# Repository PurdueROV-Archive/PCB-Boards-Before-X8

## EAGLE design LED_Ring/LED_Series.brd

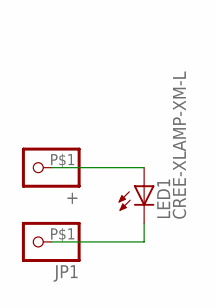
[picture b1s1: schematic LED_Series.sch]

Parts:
+: PINHD-1X1; 1X01
JP1: PINHD-1X1; 1X01
LED1: CREE-XLAMP-XM-L

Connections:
AN: JP1.P$1, LED1.C, LED1.C@1 (C)
CAT: +.P$1, LED1.A, LED1.A@1 (A)

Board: 2 copper layers, 3 parts (0 on the bottom side), 2 nets, no tracks yet.

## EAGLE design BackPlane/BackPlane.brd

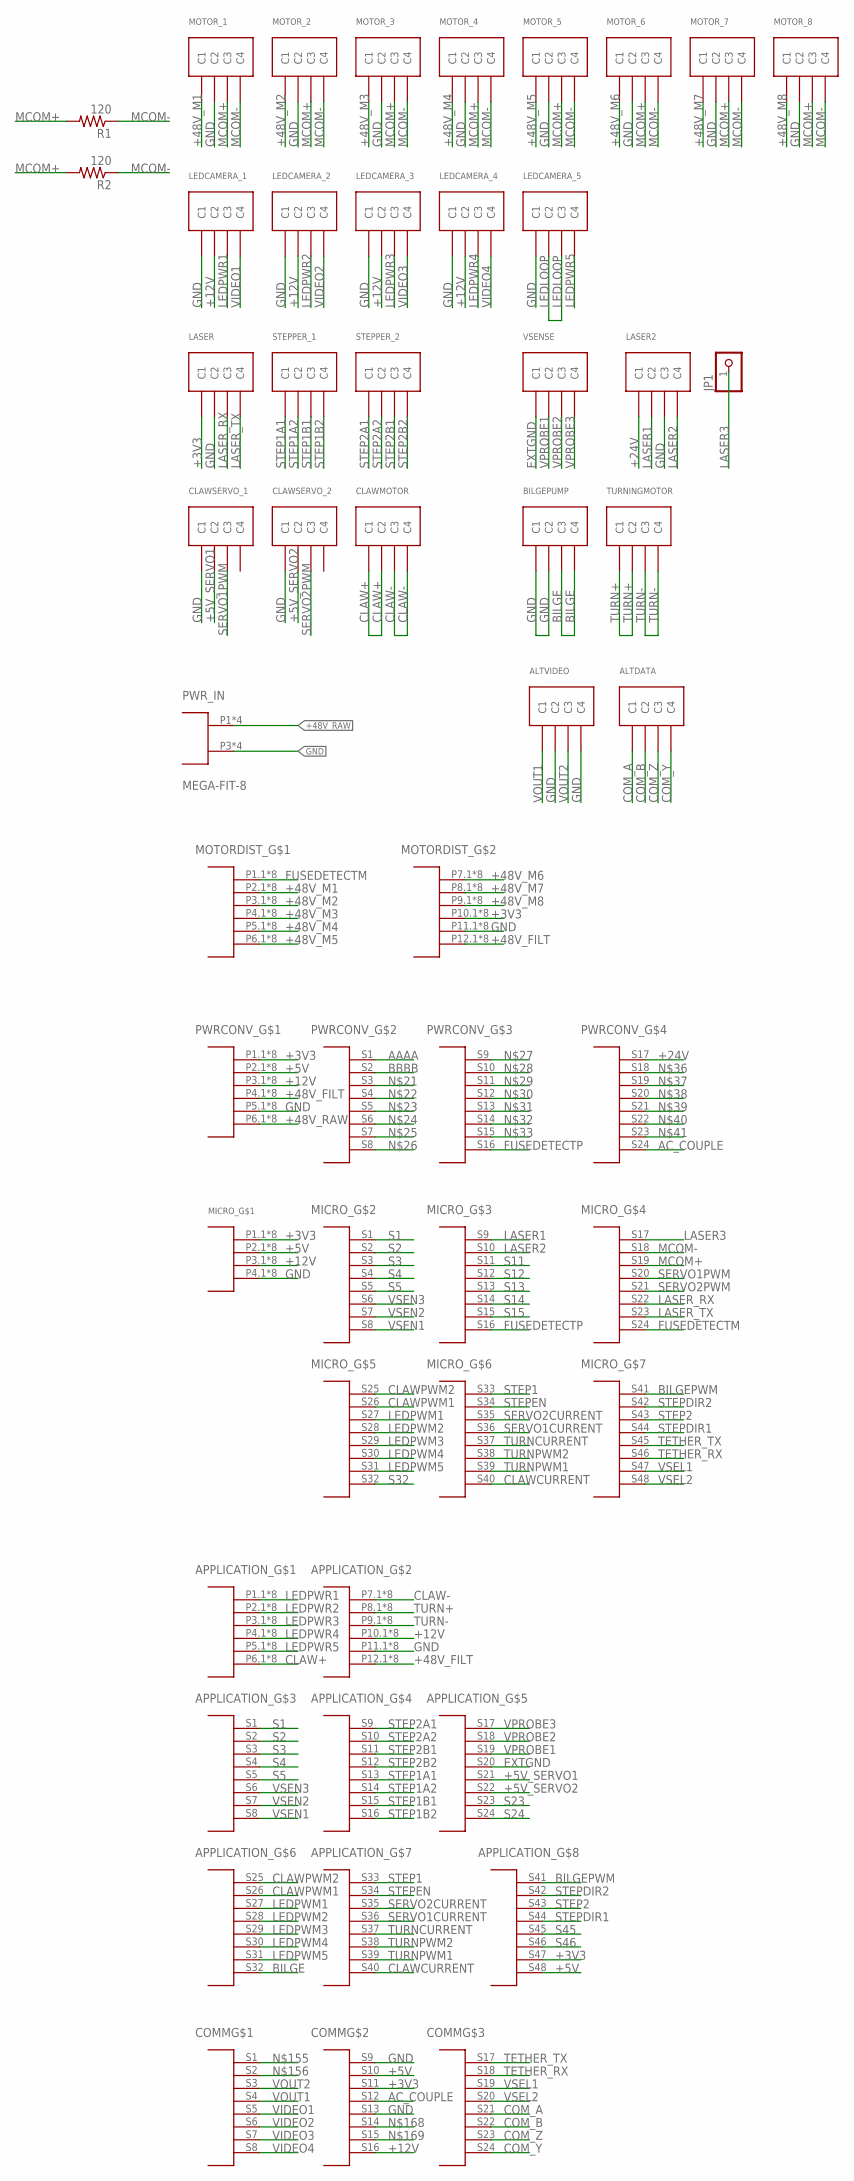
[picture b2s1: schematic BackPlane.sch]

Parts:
ALTDATA: MICRO-FIT-4-SMD-PART; MIRCO-FIT-4-SMD
ALTVIDEO: MICRO-FIT-4-SMD-PART; MIRCO-FIT-4-SMD
APPLICATION_: TEN60-P6-S24-S24-P6-VERT
BILGEPUMP: MICRO-FIT-4-SMD-PART; MIRCO-FIT-4-SMD
CLAWMOTOR: MICRO-FIT-4-SMD-PART; MIRCO-FIT-4-SMD
CLAWSERVO_1, CLAWSERVO_2: MICRO-FIT-4-SMD-PART; MIRCO-FIT-4-SMD
COMM: TEN60-S24-RA
JP1: PINHD-1X1; 1X01
LASER, LASER2: MICRO-FIT-4-SMD-PART; MIRCO-FIT-4-SMD
LEDCAMERA_1, LEDCAMERA_2, LEDCAMERA_3, LEDCAMERA_4, LEDCAMERA_5: MICRO-FIT-4-SMD-PART; MIRCO-FIT-4-SMD
MICRO_: TEN60-S24-S24-P4-VERT
MOTORDIST_: TEN60-P6-P6-VERT
MOTOR_1, MOTOR_2, MOTOR_3, MOTOR_4, MOTOR_5, MOTOR_6, MOTOR_7, MOTOR_8: MICRO-FIT-4-SMD-PART; MIRCO-FIT-4-SMD
PWRCONV_: TEN60-S24-P6-VERT
PWR_IN: MEGA-FIT-8
R1, R2: 120; R0603
STEPPER_1, STEPPER_2: MICRO-FIT-4-SMD-PART; MIRCO-FIT-4-SMD
TURNINGMOTOR: MICRO-FIT-4-SMD-PART; MIRCO-FIT-4-SMD
VSENSE: MICRO-FIT-4-SMD-PART; MIRCO-FIT-4-SMD

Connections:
+3V3: APPLICATION_.S47, COMM.S11, LASER.C1, MICRO_.P1.1, MICRO_.P1.2, MICRO_.P1.3, MICRO_.P1.4, MICRO_.P1.5, MICRO_.P1.6, MICRO_.P1.7, MICRO_.P1.8, MOTORDIST_.P10.1, MOTORDIST_.P10.2, MOTORDIST_.P10.3, MOTORDIST_.P10.4, MOTORDIST_.P10.5, MOTORDIST_.P10.6, MOTORDIST_.P10.7, MOTORDIST_.P10.8, PWRCONV_.P1.1, PWRCONV_.P1.2, PWRCONV_.P1.3, PWRCONV_.P1.4, PWRCONV_.P1.5, PWRCONV_.P1.6, PWRCONV_.P1.7, PWRCONV_.P1.8
+5V: APPLICATION_.S48, COMM.S10, MICRO_.P2.1, MICRO_.P2.2, MICRO_.P2.3, MICRO_.P2.4, MICRO_.P2.5, MICRO_.P2.6, MICRO_.P2.7, MICRO_.P2.8, PWRCONV_.P2.1, PWRCONV_.P2.2, PWRCONV_.P2.3, PWRCONV_.P2.4, PWRCONV_.P2.5, PWRCONV_.P2.6, PWRCONV_.P2.7, PWRCONV_.P2.8
+5V_SERVO1: APPLICATION_.S21, CLAWSERVO_1.C2
+5V_SERVO2: APPLICATION_.S22, CLAWSERVO_2.C2
+12V: APPLICATION_.P10.1, APPLICATION_.P10.2, APPLICATION_.P10.3, APPLICATION_.P10.4, APPLICATION_.P10.5, APPLICATION_.P10.6, APPLICATION_.P10.7, APPLICATION_.P10.8, COMM.S16, LEDCAMERA_1.C2, LEDCAMERA_2.C2, LEDCAMERA_3.C2, LEDCAMERA_4.C2, MICRO_.P3.1, MICRO_.P3.2, MICRO_.P3.3, MICRO_.P3.4, MICRO_.P3.5, MICRO_.P3.6, MICRO_.P3.7, MICRO_.P3.8, PWRCONV_.P3.1, PWRCONV_.P3.2, PWRCONV_.P3.3, PWRCONV_.P3.4, PWRCONV_.P3.5, PWRCONV_.P3.6, PWRCONV_.P3.7, PWRCONV_.P3.8
+24V: LASER2.C1, PWRCONV_.S17
+48V_FILT: APPLICATION_.P12.1, APPLICATION_.P12.2, APPLICATION_.P12.3, APPLICATION_.P12.4, APPLICATION_.P12.5, APPLICATION_.P12.6, APPLICATION_.P12.7, APPLICATION_.P12.8, MOTORDIST_.P12.1, MOTORDIST_.P12.2, MOTORDIST_.P12.3, MOTORDIST_.P12.4, MOTORDIST_.P12.5, MOTORDIST_.P12.6, MOTORDIST_.P12.7, MOTORDIST_.P12.8, PWRCONV_.P4.1, PWRCONV_.P4.2, PWRCONV_.P4.3, PWRCONV_.P4.4, PWRCONV_.P4.5, PWRCONV_.P4.6, PWRCONV_.P4.7, PWRCONV_.P4.8
+48V_M1: MOTORDIST_.P2.1, MOTORDIST_.P2.2, MOTORDIST_.P2.3, MOTORDIST_.P2.4, MOTORDIST_.P2.5, MOTORDIST_.P2.6, MOTORDIST_.P2.7, MOTORDIST_.P2.8, MOTOR_1.C1
+48V_M2: MOTORDIST_.P3.1, MOTORDIST_.P3.2, MOTORDIST_.P3.3, MOTORDIST_.P3.4, MOTORDIST_.P3.5, MOTORDIST_.P3.6, MOTORDIST_.P3.7, MOTORDIST_.P3.8, MOTOR_2.C1
+48V_M3: MOTORDIST_.P4.1, MOTORDIST_.P4.2, MOTORDIST_.P4.3, MOTORDIST_.P4.4, MOTORDIST_.P4.5, MOTORDIST_.P4.6, MOTORDIST_.P4.7, MOTORDIST_.P4.8, MOTOR_3.C1
+48V_M4: MOTORDIST_.P5.1, MOTORDIST_.P5.2, MOTORDIST_.P5.3, MOTORDIST_.P5.4, MOTORDIST_.P5.5, MOTORDIST_.P5.6, MOTORDIST_.P5.7, MOTORDIST_.P5.8, MOTOR_4.C1
+48V_M5: MOTORDIST_.P6.1, MOTORDIST_.P6.2, MOTORDIST_.P6.3, MOTORDIST_.P6.4, MOTORDIST_.P6.5, MOTORDIST_.P6.6, MOTORDIST_.P6.7, MOTORDIST_.P6.8, MOTOR_5.C1
+48V_M6: MOTORDIST_.P7.1, MOTORDIST_.P7.2, MOTORDIST_.P7.3, MOTORDIST_.P7.4, MOTORDIST_.P7.5, MOTORDIST_.P7.6, MOTORDIST_.P7.7, MOTORDIST_.P7.8, MOTOR_6.C1
+48V_M7: MOTORDIST_.P8.1, MOTORDIST_.P8.2, MOTORDIST_.P8.3, MOTORDIST_.P8.4, MOTORDIST_.P8.5, MOTORDIST_.P8.6, MOTORDIST_.P8.7, MOTORDIST_.P8.8, MOTOR_7.C1
+48V_M8: MOTORDIST_.P9.1, MOTORDIST_.P9.2, MOTORDIST_.P9.3, MOTORDIST_.P9.4, MOTORDIST_.P9.5, MOTORDIST_.P9.6, MOTORDIST_.P9.7, MOTORDIST_.P9.8, MOTOR_8.C1
+48V_RAW: PWRCONV_.P6.1, PWRCONV_.P6.2, PWRCONV_.P6.3, PWRCONV_.P6.4, PWRCONV_.P6.5, PWRCONV_.P6.6, PWRCONV_.P6.7, PWRCONV_.P6.8, PWR_IN.P1, PWR_IN.P2, PWR_IN.P5, PWR_IN.P6
AAAA: PWRCONV_.S1
AC_COUPLE: COMM.S12, PWRCONV_.S24
BBBB: PWRCONV_.S2
BILGE: APPLICATION_.S32, BILGEPUMP.C3, BILGEPUMP.C4
BILGEPWM: APPLICATION_.S41, MICRO_.S41
CLAW+: APPLICATION_.P6.1, APPLICATION_.P6.2, APPLICATION_.P6.3, APPLICATION_.P6.4, APPLICATION_.P6.5, APPLICATION_.P6.6, APPLICATION_.P6.7, APPLICATION_.P6.8, CLAWMOTOR.C1, CLAWMOTOR.C2
CLAW-: APPLICATION_.P7.1, APPLICATION_.P7.2, APPLICATION_.P7.3, APPLICATION_.P7.4, APPLICATION_.P7.5, APPLICATION_.P7.6, APPLICATION_.P7.7, APPLICATION_.P7.8, CLAWMOTOR.C3, CLAWMOTOR.C4
CLAWCURRENT: APPLICATION_.S40, MICRO_.S40
CLAWPWM1: APPLICATION_.S26, MICRO_.S26
CLAWPWM2: APPLICATION_.S25, MICRO_.S25
COM_A: ALTDATA.C1, COMM.S21
COM_B: ALTDATA.C2, COMM.S22
COM_Y: ALTDATA.C4, COMM.S24
COM_Z: ALTDATA.C3, COMM.S23
EXTGND: APPLICATION_.S20, VSENSE.C1
FUSEDETECTM: MICRO_.S24, MOTORDIST_.P1.1, MOTORDIST_.P1.2, MOTORDIST_.P1.3, MOTORDIST_.P1.4, MOTORDIST_.P1.5, MOTORDIST_.P1.6, MOTORDIST_.P1.7, MOTORDIST_.P1.8
FUSEDETECTP: MICRO_.S16, PWRCONV_.S16
GND: ALTVIDEO.C2, ALTVIDEO.C4, APPLICATION_.P11.1, APPLICATION_.P11.2, APPLICATION_.P11.3, APPLICATION_.P11.4, APPLICATION_.P11.5, APPLICATION_.P11.6, APPLICATION_.P11.7, APPLICATION_.P11.8, BILGEPUMP.C1, BILGEPUMP.C2, CLAWSERVO_1.C1, CLAWSERVO_2.C1, COMM.S9, COMM.S13, LASER.C2, LASER2.C3, LEDCAMERA_1.C1, LEDCAMERA_2.C1, LEDCAMERA_3.C1, LEDCAMERA_4.C1, LEDCAMERA_5.C1, MICRO_.P4.1, MICRO_.P4.2, MICRO_.P4.3, MICRO_.P4.4, MICRO_.P4.5, MICRO_.P4.6, MICRO_.P4.7, MICRO_.P4.8, MOTORDIST_.P11.1, MOTORDIST_.P11.2, MOTORDIST_.P11.3, MOTORDIST_.P11.4, MOTORDIST_.P11.5, MOTORDIST_.P11.6, MOTORDIST_.P11.7, MOTORDIST_.P11.8, MOTOR_1.C2, MOTOR_2.C2, MOTOR_3.C2, MOTOR_4.C2, MOTOR_5.C2, MOTOR_6.C2, MOTOR_7.C2, MOTOR_8.C2, PWRCONV_.P5.1, PWRCONV_.P5.2, PWRCONV_.P5.3, PWRCONV_.P5.4, PWRCONV_.P5.5, PWRCONV_.P5.6, PWRCONV_.P5.7, PWRCONV_.P5.8, PWR_IN.P3, PWR_IN.P4, PWR_IN.P7, PWR_IN.P8
LASER1: LASER2.C2, MICRO_.S9
LASER2: LASER2.C4, MICRO_.S10
LASER3: JP1.1, MICRO_.S17
LASER_RX: LASER.C3, MICRO_.S22
LASER_TX: LASER.C4, MICRO_.S23
LEDLOOP: LEDCAMERA_5.C2, LEDCAMERA_5.C3
LEDPWM1: APPLICATION_.S27, MICRO_.S27
LEDPWM2: APPLICATION_.S28, MICRO_.S28
LEDPWM3: APPLICATION_.S29, MICRO_.S29
LEDPWM4: APPLICATION_.S30, MICRO_.S30
LEDPWM5: APPLICATION_.S31, MICRO_.S31
LEDPWR1: APPLICATION_.P1.1, APPLICATION_.P1.2, APPLICATION_.P1.3, APPLICATION_.P1.4, APPLICATION_.P1.5, APPLICATION_.P1.6, APPLICATION_.P1.7, APPLICATION_.P1.8, LEDCAMERA_1.C3
LEDPWR2: APPLICATION_.P2.1, APPLICATION_.P2.2, APPLICATION_.P2.3, APPLICATION_.P2.4, APPLICATION_.P2.5, APPLICATION_.P2.6, APPLICATION_.P2.7, APPLICATION_.P2.8, LEDCAMERA_2.C3
LEDPWR3: APPLICATION_.P3.1, APPLICATION_.P3.2, APPLICATION_.P3.3, APPLICATION_.P3.4, APPLICATION_.P3.5, APPLICATION_.P3.6, APPLICATION_.P3.7, APPLICATION_.P3.8, LEDCAMERA_3.C3
LEDPWR4: APPLICATION_.P4.1, APPLICATION_.P4.2, APPLICATION_.P4.3, APPLICATION_.P4.4, APPLICATION_.P4.5, APPLICATION_.P4.6, APPLICATION_.P4.7, APPLICATION_.P4.8, LEDCAMERA_4.C3
LEDPWR5: APPLICATION_.P5.1, APPLICATION_.P5.2, APPLICATION_.P5.3, APPLICATION_.P5.4, APPLICATION_.P5.5, APPLICATION_.P5.6, APPLICATION_.P5.7, APPLICATION_.P5.8, LEDCAMERA_5.C4
MCOM+: MICRO_.S19, MOTOR_1.C3, MOTOR_2.C3, MOTOR_3.C3, MOTOR_4.C3, MOTOR_5.C3, MOTOR_6.C3, MOTOR_7.C3, MOTOR_8.C3, R1.2, R2.2
MCOM-: MICRO_.S18, MOTOR_1.C4, MOTOR_2.C4, MOTOR_3.C4, MOTOR_4.C4, MOTOR_5.C4, MOTOR_6.C4, MOTOR_7.C4, MOTOR_8.C4, R1.1, R2.1
S1: APPLICATION_.S1, MICRO_.S1
S2: APPLICATION_.S2, MICRO_.S2
S3: APPLICATION_.S3, MICRO_.S3
S4: APPLICATION_.S4, MICRO_.S4
S5: APPLICATION_.S5, MICRO_.S5
S11: MICRO_.S11
S12: MICRO_.S12
S13: MICRO_.S13
S14: MICRO_.S14
S15: MICRO_.S15
S23: APPLICATION_.S23
S24: APPLICATION_.S24
S32: MICRO_.S32
S45: APPLICATION_.S45
S46: APPLICATION_.S46
SERVO1CURRENT: APPLICATION_.S36, MICRO_.S36
SERVO1PWM: CLAWSERVO_1.C3, MICRO_.S20
SERVO2CURRENT: APPLICATION_.S35, MICRO_.S35
SERVO2PWM: CLAWSERVO_2.C3, MICRO_.S21
STEP1: APPLICATION_.S33, MICRO_.S33
STEP1A1: APPLICATION_.S13, STEPPER_1.C1
STEP1A2: APPLICATION_.S14, STEPPER_1.C2
STEP1B1: APPLICATION_.S15, STEPPER_1.C3
STEP1B2: APPLICATION_.S16, STEPPER_1.C4
STEP2: APPLICATION_.S43, MICRO_.S43
STEP2A1: APPLICATION_.S9, STEPPER_2.C1
STEP2A2: APPLICATION_.S10, STEPPER_2.C2
STEP2B1: APPLICATION_.S11, STEPPER_2.C3
STEP2B2: APPLICATION_.S12, STEPPER_2.C4
STEPDIR1: APPLICATION_.S44, MICRO_.S44
STEPDIR2: APPLICATION_.S42, MICRO_.S42
STEPEN: APPLICATION_.S34, MICRO_.S34
TETHER_RX: COMM.S18, MICRO_.S46
TETHER_TX: COMM.S17, MICRO_.S45
TURN+: APPLICATION_.P8.1, APPLICATION_.P8.2, APPLICATION_.P8.3, APPLICATION_.P8.4, APPLICATION_.P8.5, APPLICATION_.P8.6, APPLICATION_.P8.7, APPLICATION_.P8.8, TURNINGMOTOR.C1, TURNINGMOTOR.C2
TURN-: APPLICATION_.P9.1, APPLICATION_.P9.2, APPLICATION_.P9.3, APPLICATION_.P9.4, APPLICATION_.P9.5, APPLICATION_.P9.6, APPLICATION_.P9.7, APPLICATION_.P9.8, TURNINGMOTOR.C3, TURNINGMOTOR.C4
TURNCURRENT: APPLICATION_.S37, MICRO_.S37
TURNPWM1: APPLICATION_.S39, MICRO_.S39
TURNPWM2: APPLICATION_.S38, MICRO_.S38
VIDEO1: COMM.S5, LEDCAMERA_1.C4
VIDEO2: COMM.S6, LEDCAMERA_2.C4
VIDEO3: COMM.S7, LEDCAMERA_3.C4
VIDEO4: COMM.S8, LEDCAMERA_4.C4
VOUT1: ALTVIDEO.C1, COMM.S4
VOUT2: ALTVIDEO.C3, COMM.S3
VPROBE1: APPLICATION_.S19, VSENSE.C2
VPROBE2: APPLICATION_.S18, VSENSE.C3
VPROBE3: APPLICATION_.S17, VSENSE.C4
VSEL1: COMM.S19, MICRO_.S47
VSEL2: COMM.S20, MICRO_.S48
VSEN1: APPLICATION_.S8, MICRO_.S8
VSEN2: APPLICATION_.S7, MICRO_.S7
VSEN3: APPLICATION_.S6, MICRO_.S6

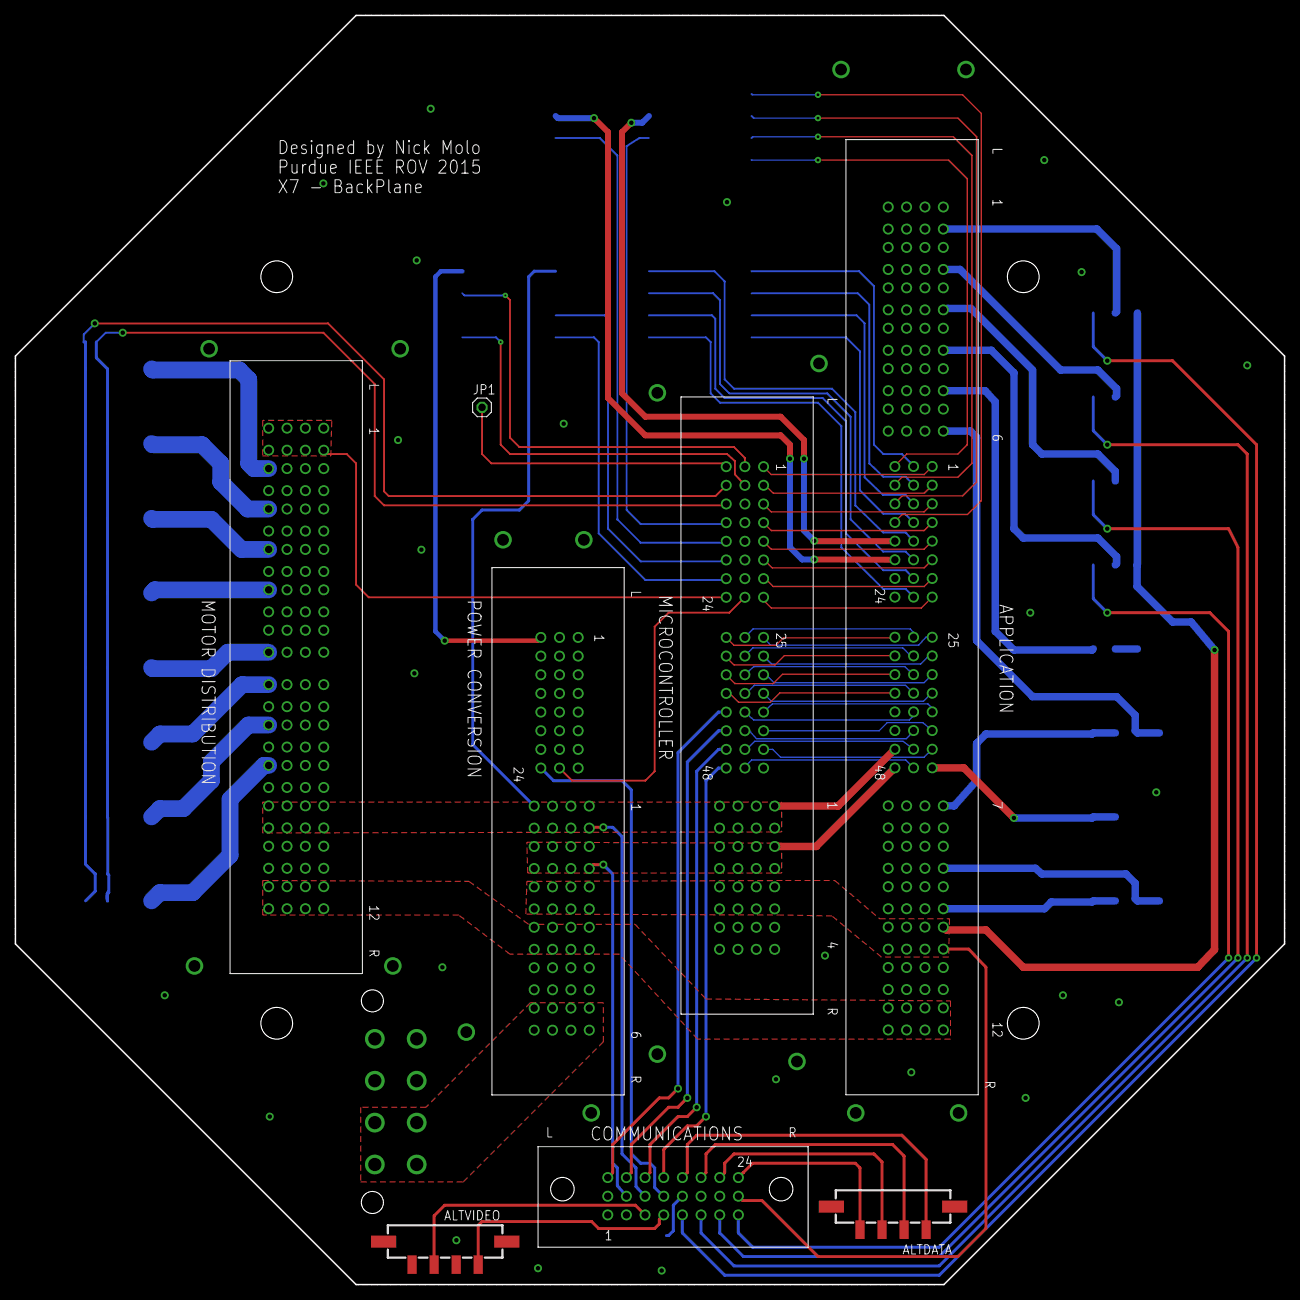
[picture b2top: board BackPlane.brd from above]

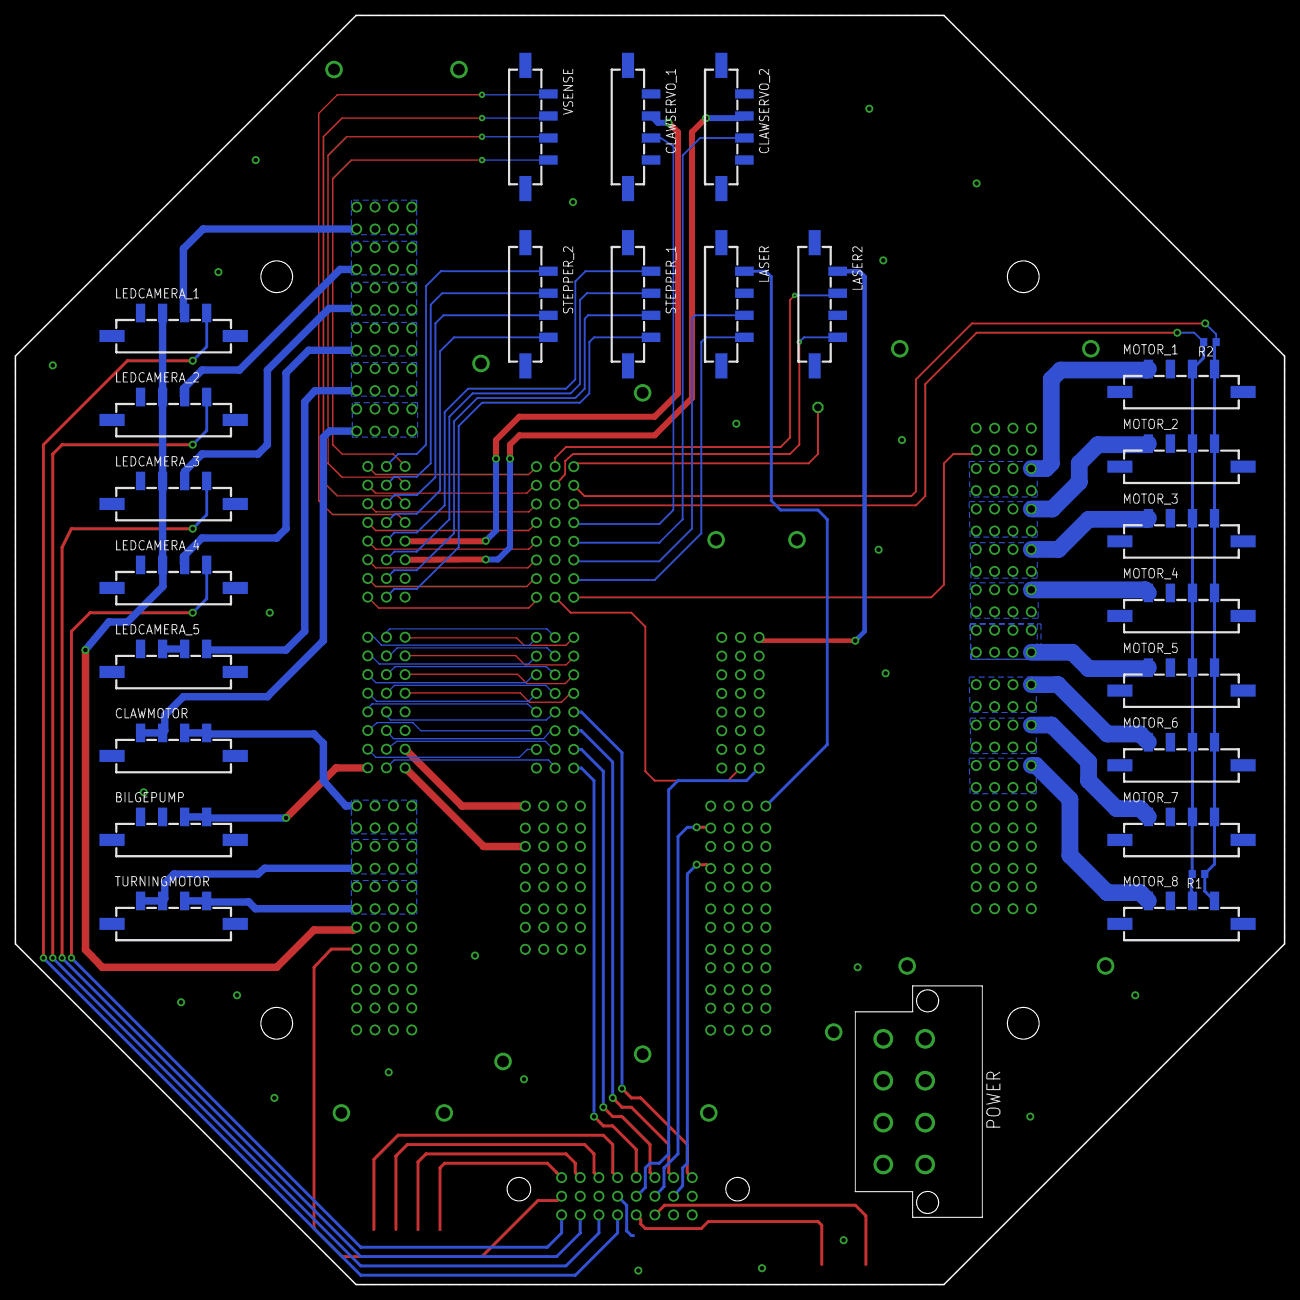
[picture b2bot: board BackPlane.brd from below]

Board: 2 copper layers, 172.7 x 172.7 mm, 34 parts (26 on the bottom side), 93 nets.

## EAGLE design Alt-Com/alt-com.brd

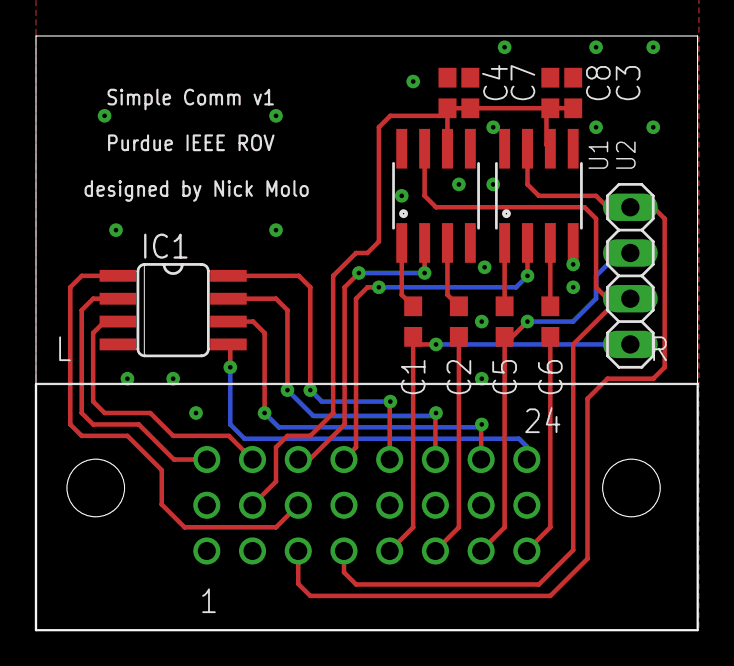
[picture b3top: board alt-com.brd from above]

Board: 2 copper layers, 36.8 x 33.0 mm, 13 parts (0 on the bottom side), 21 nets.

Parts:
C1, C2, C5, C6: 0.01uF; C0603
C3, C7: 0.1uF; C0603
C4, C8: 47uF; C0603
EMEREGENCY: 1X04
IC1: MAX3467CPA; SO08
U1, U2: SO08
U$1: TEN60-S24-RA

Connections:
+3V3: IC1.1, U$1.S11
+5V: C3.1, C4.1, C7.1, C8.1, U1.6, U2.6, U$1.S10
COM_A: IC1.8, U$1.S21
COM_B: IC1.7, U$1.S22
COM_Y: IC1.5, U$1.S24
COM_Z: IC1.6, U$1.S23
GND: C3.2, C4.2, C7.2, C8.2, IC1.4, U1.4, U1.8, U2.4, U2.8, U$1.S9
unnamed: C5.1, U2.1
unnamed: C6.1, U2.3
unnamed: C1.1, U1.1
unnamed: C2.1, U1.3
TETHER_RX: IC1.2, U$1.S17
TETHER_TX: IC1.3, U$1.S18
VIDEO1: C1.2, EMEREGENCY.1, U$1.S5
VIDEO2: C2.2, U$1.S6
VIDEO3: C5.2, EMEREGENCY.3, U$1.S7
VIDEO4: C6.2, U$1.S8
VOUT1: EMEREGENCY.2, U1.7, U$1.S4
VOUT2: EMEREGENCY.4, U2.7, U$1.S3
VSEL1: U1.2, U$1.S19
VSEL2: U2.2, U$1.S20

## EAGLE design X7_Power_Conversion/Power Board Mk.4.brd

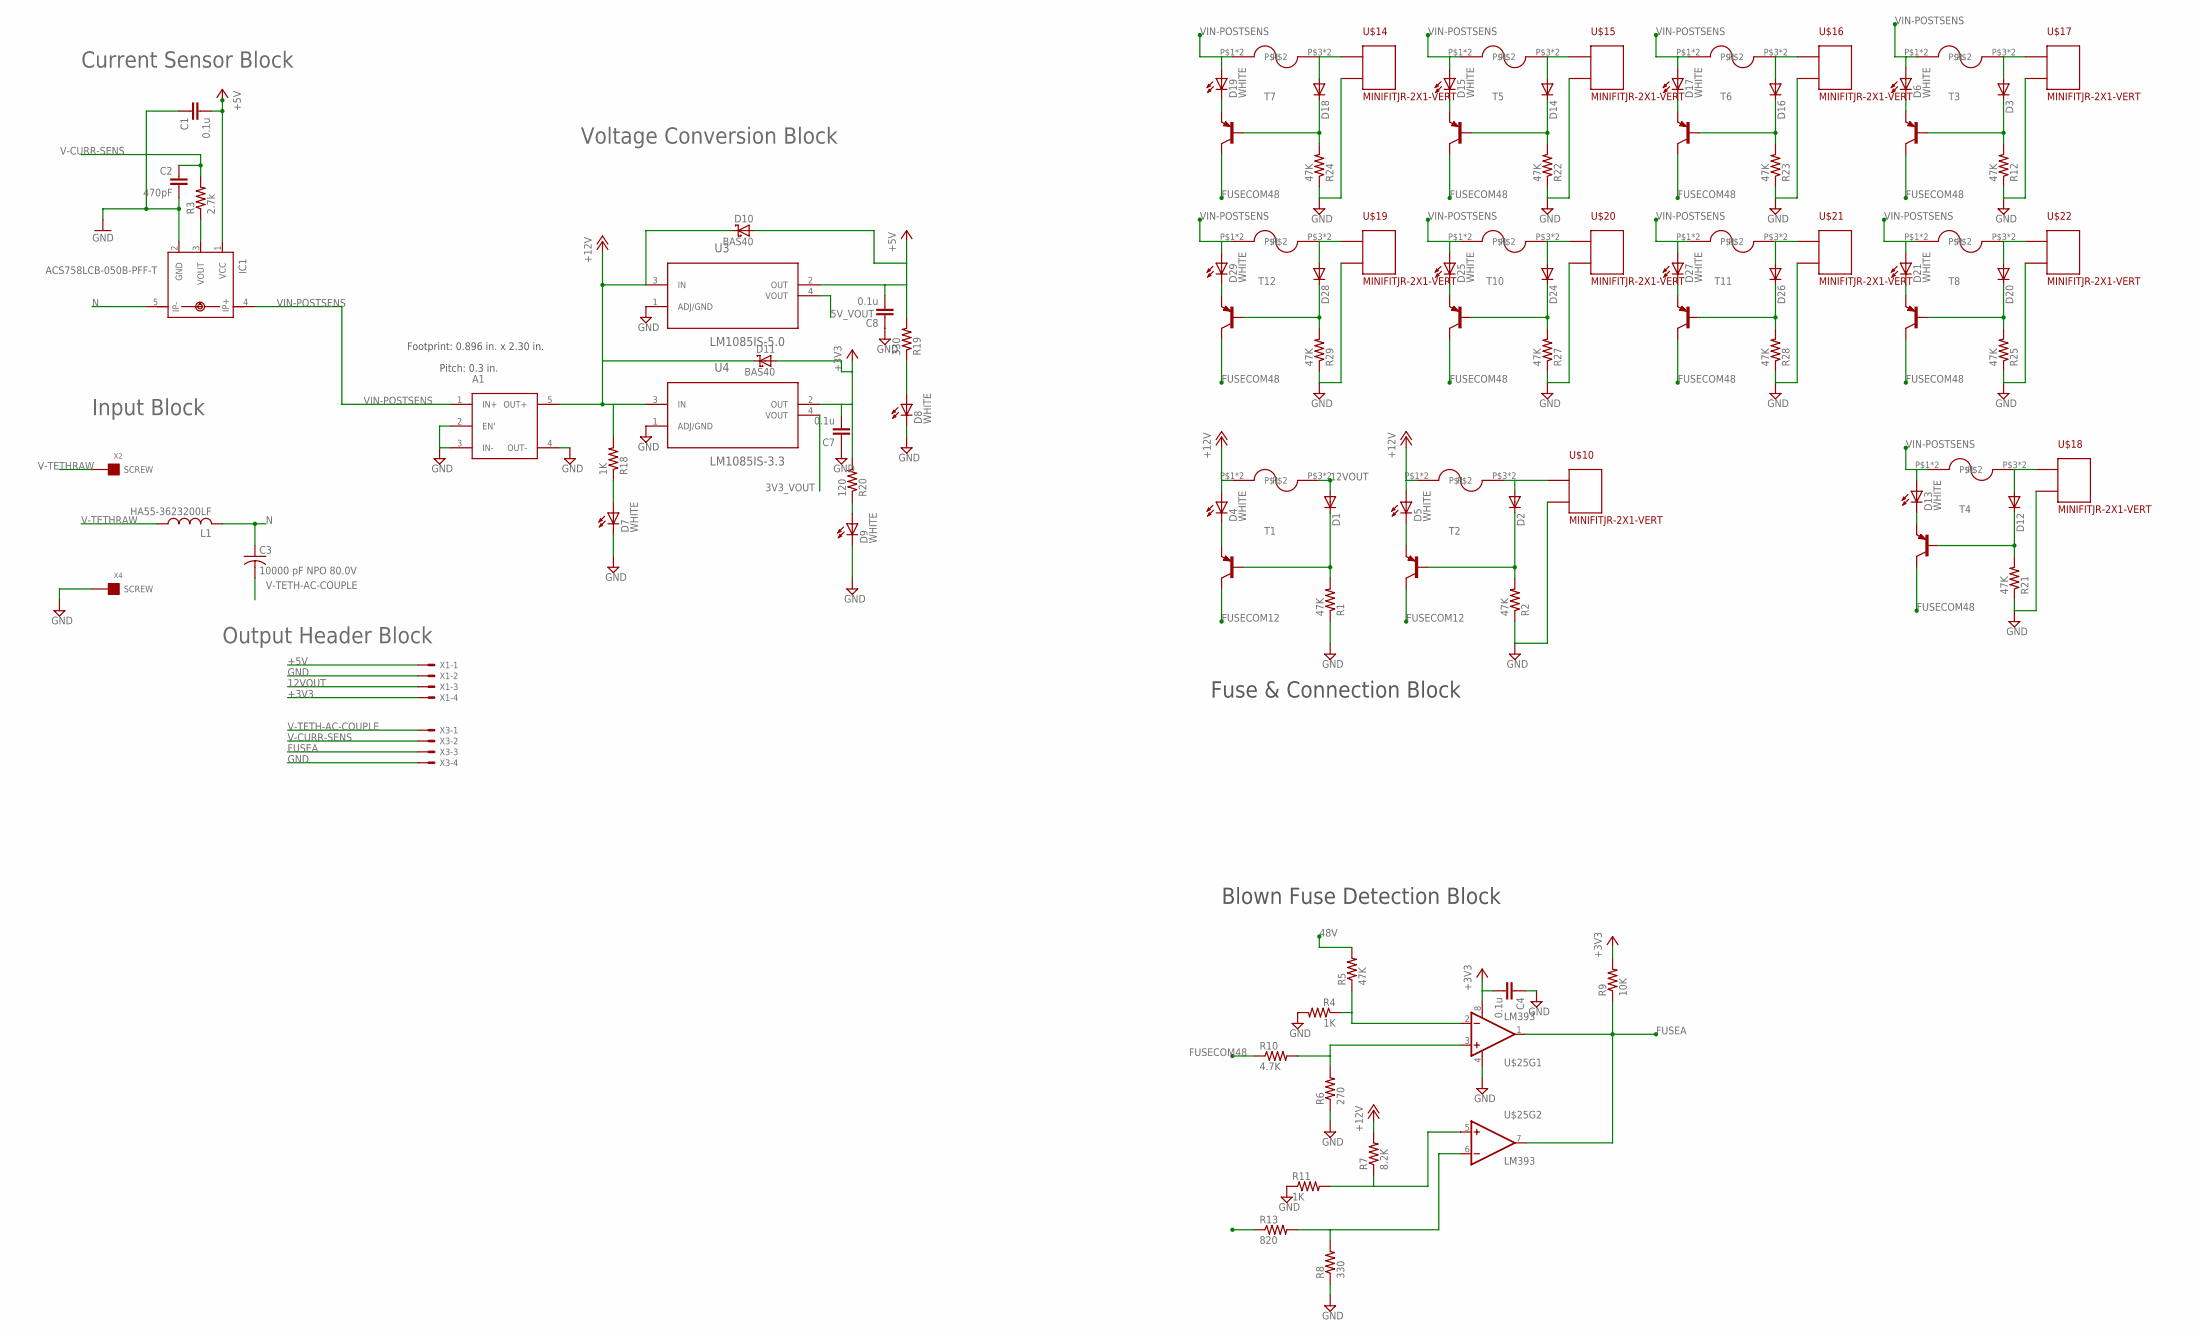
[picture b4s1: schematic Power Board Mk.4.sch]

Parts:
A1: SQE48T20120; BRICK
C1, C4, C7, C8: 0.1u; 0805
C2: 470pF; 0805
C3: 10000 pF NPO 80.0V; C0603
D1, D2, D3, D12, D14, D16, D18, D20, D24, D26, D28: DIODEHV; DIODE-HV
D4, D5, D6, D7, D8, D9, D13, D15, D17, D19, D21, D25, D27, D29: WHITE; LED-1206
D10, D11: BAS40; SOT23
IC1: ACS758LCB-050B-PFF-T; CB-PFF
L1: HA55-3623200LF; THIND
R1, R2, R5, R12, R21, R22, R23, R24, R25, R27, R28, R29: 47K; 0805
R3: 2.7k; 0805
R4, R11, R18: 1K; 0805
R6: 270; 0805
R7: 8.2K; 0805
R8, R19: 330; 0805
R9: 10K; 0805
R10: 4.7K; 0805
R13: 820; 0805
R20: 120; 0805
T1, T2, T3, T4, T5, T6, T7, T8, T10, T11, T12: BC856BLT1-PNP-SOT23-BEC; SOT23-BEC
U3: LM1085IS-5.0; TO254P1435X457-3N
U4: LM1085IS-3.3; TO254P1435X457-3N
U$2, U$3, U$4, U$5, U$6, U$7, U$8, U$9, U$11, U$12, U$13: FUSEHOLDER3557-2
U$10, U$14, U$15, U$16, U$17, U$18, U$19, U$20, U$21, U$22: MINIFITJR-2X1-VERT; 5566-02B
U$25: LM393; SO08
X1, X3: KK-156-4
X2, X4: SCREW_TERM; TERMINAL

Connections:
3V3_VOUT: U4.4 (VOUT)
5V_VOUT: U3.4 (VOUT)
12VOUT: D1.A, U$4.P$3, U$4.P$4, X1.3
12VOUT1: D2.A, U$3.P$3, U$3.P$4, U$10.P$1
48V: R5.2
+3V3: C4.2, C7.2, D11.1 (A), R9.2, R20.2, U4.2 (OUT), U$25.8 (V+), X1.4
+5V: C1.2, C8.2, D10.1 (A), IC1.1 (VCC), R19.2, U3.2 (OUT), X1.1
+12V: A1.5 (OUT+), D4.A, D5.A, D10.3 (C), D11.3 (C), R7.2, R18.2, U3.3 (IN), U4.3 (IN), U$3.P$1, U$3.P$2, U$4.P$1, U$4.P$2
FUSEA: R9.1, U$25.1 (OUT), U$25.7 (OUT), X3.3
FUSECOM12: R13.1, T1.C, T2.C
FUSECOM48: R10.1, T3.C, T4.C, T5.C, T6.C, T7.C, T8.C, T10.C, T11.C, T12.C
GND: A1.2 (EN'), A1.3 (IN-), A1.4 (OUT-), C1.1, C2.2, C4.1, C7.1, C8.1, D7.C, D8.C, D9.C, IC1.2 (GND), R1.1, R2.1, R4.2, R6.1, R8.1, R11.1, R12.1, R21.1, R22.1, R23.1, R24.1, R25.1, R27.1, R28.1, R29.1, U3.1 (ADJ/GND), U4.1 (ADJ/GND), U$10.P$2, U$14.P$2, U$15.P$2, U$16.P$2, U$17.P$2, U$18.P$2, U$19.P$2, U$20.P$2, U$21.P$2, U$22.P$2, U$25.4 (V-), X1.2, X3.4, X4.P$1, X4.P$2, X4.P$3, X4.P$4, X4.P$5, X4.P$6, X4.P$7, X4.P$8, X4.P$9, X4.P$10
N: C3.1, IC1.5 (IP-), L1.2
unnamed: R4.1, R5.1, U$25.2 (-IN)
unnamed: IC1.3 (VOUT), R3.1
unnamed: R6.2, R10.2, U$25.3 (+IN)
unnamed: R7.1, R11.2, U$25.5 (+IN)
unnamed: R8.2, R13.2, U$25.6 (-IN)
unnamed: D2.C, R2.2, T2.B
unnamed: D5.C, T2.E
unnamed: D3.A, U$2.P$3, U$2.P$4, U$17.P$1
unnamed: D3.C, R12.2, T3.B
unnamed: D6.C, T3.E
unnamed: D1.C, R1.2, T1.B
unnamed: D4.C, T1.E
unnamed: D7.A, R18.1
unnamed: D8.A, R19.1
unnamed: D9.A, R20.1
unnamed: D12.C, R21.2, T4.B
unnamed: D13.C, T4.E
unnamed: D12.A, U$5.P$3, U$5.P$4, U$18.P$1
unnamed: D14.C, R22.2, T5.B
unnamed: D15.C, T5.E
unnamed: D14.A, U$6.P$3, U$6.P$4, U$15.P$1
unnamed: D16.C, R23.2, T6.B
unnamed: D17.C, T6.E
unnamed: D16.A, U$7.P$3, U$7.P$4, U$16.P$1
unnamed: D18.C, R24.2, T7.B
unnamed: D19.C, T7.E
unnamed: D18.A, U$8.P$3, U$8.P$4, U$14.P$1
unnamed: D20.C, R25.2, T8.B
unnamed: D21.C, T8.E
unnamed: D20.A, U$9.P$3, U$9.P$4, U$22.P$1
unnamed: D24.C, R27.2, T10.B
unnamed: D25.C, T10.E
unnamed: D24.A, U$11.P$3, U$11.P$4, U$20.P$1
unnamed: D26.C, R28.2, T11.B
unnamed: D27.C, T11.E
unnamed: D26.A, U$12.P$3, U$12.P$4, U$21.P$1
unnamed: D28.C, R29.2, T12.B
unnamed: D29.C, T12.E
unnamed: D28.A, U$13.P$3, U$13.P$4, U$19.P$1
V-CURR-SENS: C2.1, R3.2, X3.2
V-TETH-AC-COUPLE: C3.2, X3.1
V-TETHRAW: L1.1, X2.P$1, X2.P$2, X2.P$3, X2.P$4, X2.P$5, X2.P$6, X2.P$7, X2.P$8, X2.P$9, X2.P$10
VIN-POSTSENS: A1.1 (IN+), D6.A, D13.A, D15.A, D17.A, D19.A, D21.A, D25.A, D27.A, D29.A, IC1.4 (IP+), U$2.P$1, U$2.P$2, U$5.P$1, U$5.P$2, U$6.P$1, U$6.P$2, U$7.P$1, U$7.P$2, U$8.P$1, U$8.P$2, U$9.P$1, U$9.P$2, U$11.P$1, U$11.P$2, U$12.P$1, U$12.P$2, U$13.P$1, U$13.P$2

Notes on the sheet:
Footprint: 0.896 in. x 2.30 in.
Pitch: 0.3 in.
Blown Fuse Detection Block
Fuse & Connection Block
Output Header Block
Input Block
Current Sensor Block
Voltage Conversion Block

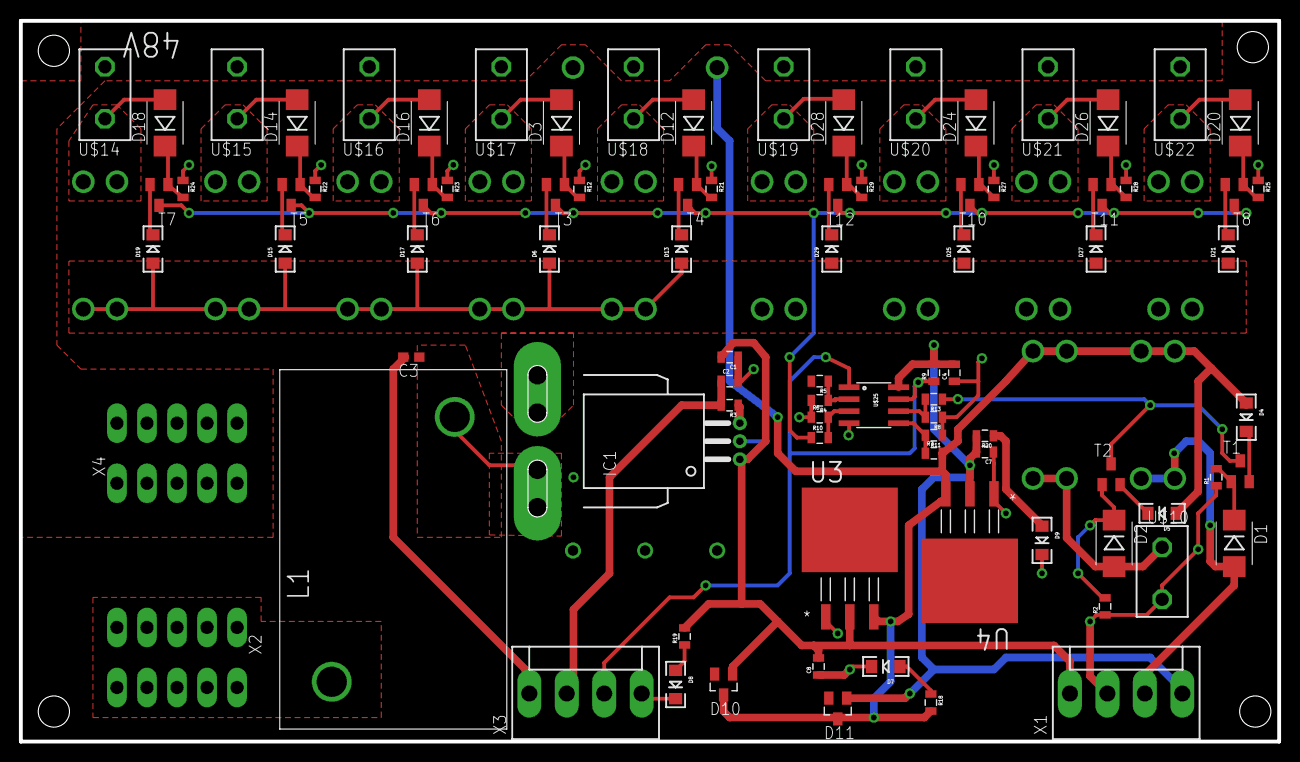
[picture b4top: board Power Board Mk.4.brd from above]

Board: 2 copper layers, 133.0 x 76.2 mm, 103 parts (1 on the bottom side), 53 nets.

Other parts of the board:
U$23, U$24, U$28, U$29: STAND-OFF

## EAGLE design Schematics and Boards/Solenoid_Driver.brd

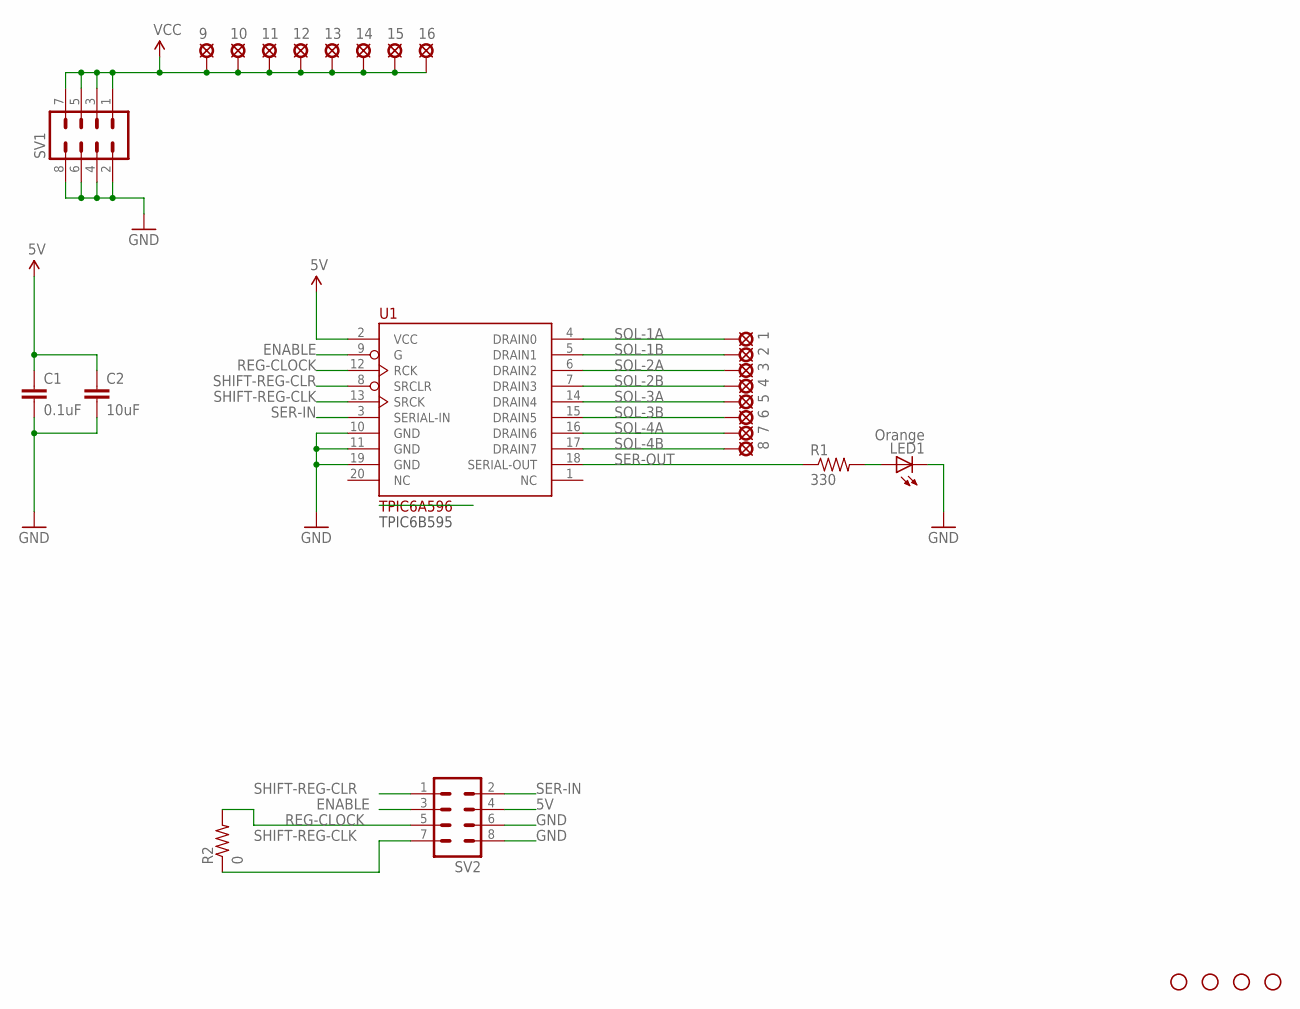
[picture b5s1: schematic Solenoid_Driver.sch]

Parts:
1, 2, 3, 4, 5, 6, 7, 8, 9, 10, 11, 12, 13, 14, 15, 16: SE14
C1: 0.1uF; 0603-CAP
C2: 10uF; 0603-CAP
JP1, JP2, JP3, JP4: STAND-OFF
LED1: Orange; LED-0603
R1: 330; 0603-RES
R2: 0; 0603-RES
SV1, SV2: MA04-2
U1: TPIC6A596; SOIC20-W

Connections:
5V: C1.1, C2.1, SV2.4, U1.2 (VCC)
ENABLE: SV2.3, U1.9 (G)
GND: C1.2, C2.2, LED1.C, SV1.2, SV1.4, SV1.6, SV1.8, SV2.6, SV2.8, U1.10 (GND), U1.11 (GND), U1.19 (GND)
unnamed: LED1.A, R1.2
REG-CLOCK: R2.2, SV2.5, U1.12 (RCK)
SER-IN: SV2.2, U1.3 (SERIAL-IN)
SER-OUT: R1.1, U1.18 (SERIAL-OUT)
SHIFT-REG-CLK: R2.1, SV2.7, U1.13 (SRCK)
SHIFT-REG-CLR: SV2.1, U1.8 (SRCLR)
SOL-1A: 1.MP, U1.4 (DRAIN0)
SOL-1B: 2.MP, U1.5 (DRAIN1)
SOL-2A: 3.MP, U1.6 (DRAIN2)
SOL-2B: 4.MP, U1.7 (DRAIN3)
SOL-3A: 5.MP, U1.14 (DRAIN4)
SOL-3B: 6.MP, U1.15 (DRAIN5)
SOL-4A: 7.MP, U1.16 (DRAIN6)
SOL-4B: 8.MP, U1.17 (DRAIN7)
VCC: 9.MP, 10.MP, 11.MP, 12.MP, 13.MP, 14.MP, 15.MP, 16.MP, SV1.1, SV1.3, SV1.5, SV1.7

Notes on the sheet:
TPIC6B595

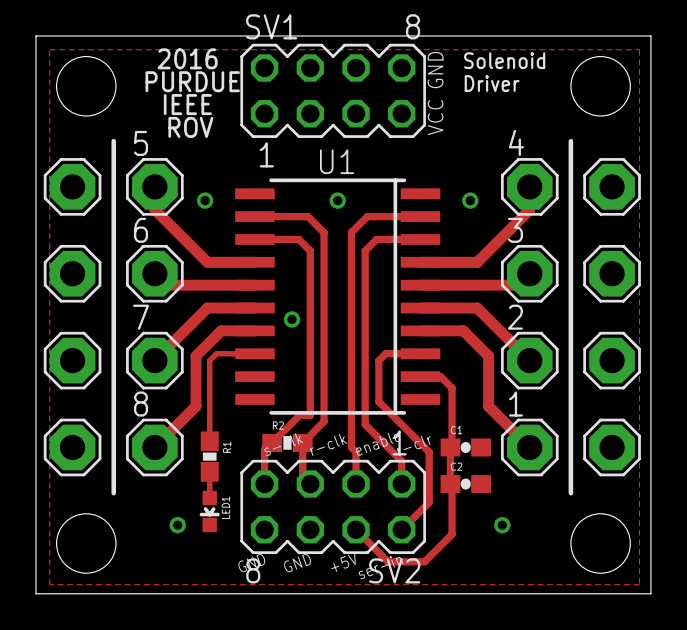
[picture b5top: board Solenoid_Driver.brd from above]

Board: 2 copper layers, 34.2 x 31.0 mm, 28 parts (0 on the bottom side), 18 nets.

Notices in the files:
parts and their libraries:
SparkFun-Aesthetics: Licensing: Creative Commons ShareAlike 4.0 International - https://creativecommons.org/licenses/by-sa/4.0
SparkFun: Licensing: CC v3.0 Share-Alike You are welcome to use this library for commercial purposes.
rc-master: Copyright (C) 2007, Bob Starr
